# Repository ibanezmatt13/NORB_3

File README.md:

WARNING - There is a slight design issue with the schematic for the PCB which I had to bodge to get the micro SD working. The VSS pins of the connector should be connected to a GND point on the board, which for some reason it isn't. So, I had to solder a wire going from the connector to a ground point on the board; not pretty but it works.

There are two scripts here, one for delay-driven RTTY, and one for interrupt-driven RTTY. The delay-driven code has been flown and proved to work perfectly; the interrupt-driven code works fine on the ground but has not had an approval flight just yet.

NORB 3
======
NORB 3 is the third generation in the NORB AVR-based HAB tracking PCB series. 

Main Components:
================

NTX2 434MHz Radio Transmitter

Ublox MAX 7 GPS Module

Amtel ATMEGA328P-AU Microcontroller

SHT11 Temperature/Humidity Sensor

TMP102 I2C Temperature Sensor

Micro SD socket

TPS61201 Step-up Boost Regulator

Taoglas GPS Antenna

Info
====

More information including the development, current status and pictures of the tracker can be found at NORB's website:

                                                  http://www.norb.co.uk

What NORB does...
=================

The current software that runs the NORB board does several things:

1.  It uses a special routine to search repeatedly for certain characters over a serial connection to the Ublox GPS         module. Once it picks up the correct beginning of what could be a valid NMEA sentence, it checks for the letter G to     to see if it is the correct sentence. If it is, it passes the sentence as a string to a parse_NMEA function.

2.  The parse_NMEA function is designed to carefully assess whether the sentence contains any anomalies in certain          fields. This could be a lost character during transfer or the sentence may not actually reflect a full GPS lock.        Should this be the case, the parsing is discontinued and the search for another sentence restarts. If it does get       through however, a few tasks are performed...

3.  The time is checked to assess what format it is in and to assess if it is a valid time value. Then the                  Latitude/longitude is converted into decimal degrees for uploading to the spacenear.us server after decoding. 

4.  After the sentence has been stripped down and individual fields of data have been analysed, the program will request     information from the SHT11 temperature and humidity sensor where upon it will parse the data into a suitable format.     The voltage across the battery is also analysed by scaling the analogue value on the correct analogue pin to a value     within the range 0v to 3.3v.

5.  Next, two strings are constructed: a log_datastring and a send_datastring. The log_datastring contains absolutely       all data including voltage and humidity, which will be logged to the SD card. The send_datastring contains only the     bare minimum of required data for basic telemetry, but I couldn't resist adding temperature in there too. I have        done this to further reduce the probability of a decoding error on the ground. ie, more data coming down = more         chance of a bad sentence.

6.  Then, we log the log_datastring to the SD card, and send the send_datastring down over the radio link by splitting      it up into binary digits to toggle the transmit pin on our transmitter. And there you have it! :D

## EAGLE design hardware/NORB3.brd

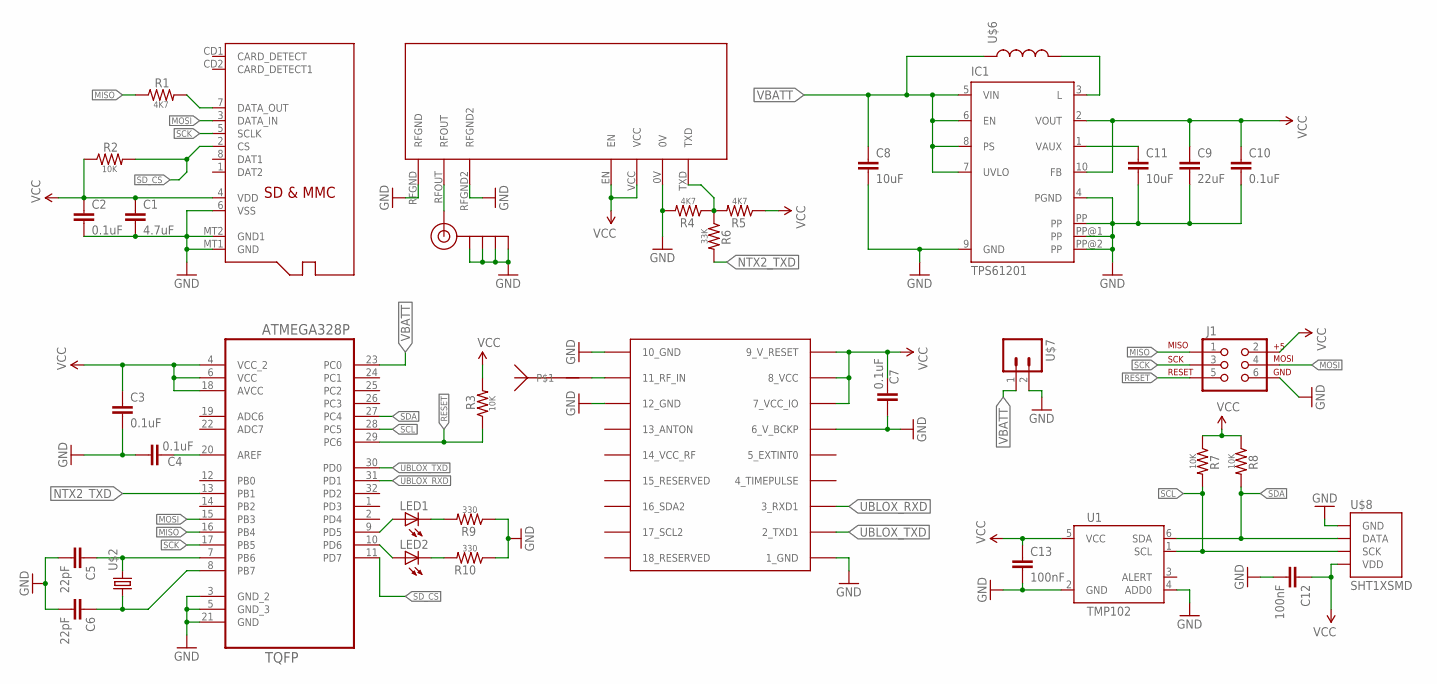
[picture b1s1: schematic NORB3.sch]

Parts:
C1: 4.7uF; 0603-CAP
C2, C3, C4, C7, C10: 0.1uF; 0603-CAP
C5, C6: 22pF; 0603-CAP
C8: 10uF; 1206
C9: 22uF; 1206
C11: 10uF; 0603-CAP
C12, C13: 100nF; 0603-CAP
IC1: TPS61201; S-PDSO-N10
J1: AVR_SPI_PRG_6PTH; 2X3
J$1: SMA_EDGE; SMA-EDGE
LED1, LED2: LEDCHIPLED_0805; CHIPLED_0805
R1, R4, R5: 4K7; 0603-RES
R2, R3, R7, R8: 10K; 0603-RES
R6: 33K; 0603-RES
R9, R10: 330; 0603-RES
U1: TMP102; SOT563
U2: ATMEGA328P-AU; QFP80P900X900X120-32N
U$1: MICROSD
U$2: ABRACON_ABM3_CRYSTALABM03_HC49; ABM03_HC49
U$3: UBLOX_MAX-6
U$4: TAOGLAS.GP.1575.18.2.A.02
U$5: NTX2
U$6: 2.2uH; ELLVGG_INDUCTOR
U$7: M02-NOSILK
U$8: SHT1XSMD; SHT1X

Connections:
GND: C3.2, C4.2, C5.2, C6.2, C7.2, C8.2, C9.2, C10.2, C11.2, C12.2, C13.2, IC1.4 (PGND), IC1.9 (GND), IC1.PP, IC1.PP@1 (PP), IC1.PP@2 (PP), J1.6, J$1.GND@0 (GND), J$1.GND@1 (GND), J$1.GND@2 (GND), J$1.GND@3 (GND), R4.2, R9.1, R10.1, U1.2 (GND), U1.4 (ADD0), U2.3 (GND_2), U2.5 (GND_3), U2.21 (GND), U$3.1_GND, U$3.6_V_BCKP, U$3.10_GND, U$3.12_GND, U$5.0V, U$5.RFGND, U$5.RFGND2, U$7.2, U$8.1 (GND)
MISO: J1.1, R1.1, U2.16 (PB4)
MOSI: J1.4, U2.15 (PB3), U$1.3 (DATA_IN)
unnamed: R1.2, U$1.7 (DATA_OUT)
unnamed: C5.1, U2.7 (PB6), U$2.2
unnamed: C4.1, U2.20 (AREF)
unnamed: C6.1, U2.8 (PB7), U$2.1
unnamed: U$3.11_RF_IN, U$4.P$1
unnamed: J$1.SIG (SIGNAL), U$5.RFOUT
unnamed: IC1.3 (L), U$6.P$2 (2)
unnamed: R4.1, R5.2, R6.1, U$5.TXD
unnamed: LED1.A, U2.9 (PD5)
unnamed: C11.1, IC1.1 (VAUX)
unnamed: LED1.C, R9.2
unnamed: LED2.A, U2.10 (PD6)
unnamed: LED2.C, R10.2
NTX2_TXD: R6.2, U2.13 (PB1)
RESET: J1.5, R3.1, U2.29 (PC6)
SCK: J1.3, U2.17 (PB5), U$1.5 (SCLK)
SCL: R7.2, U1.1 (SCL), U2.28 (PC5), U$8.3 (SCK)
SDA: R8.2, U1.6 (SDA), U2.27 (PC4), U$8.2 (DATA)
SD_CS: R2.2, U2.11 (PD7), U$1.2 (CS)
UBLOX_RXD: U2.31 (PD1), U$3.3_RXD1
UBLOX_TXD: U2.30 (PD0), U$3.2_TXD1
VBATT: C8.1, IC1.5 (VIN), IC1.6 (EN), IC1.7 (UVLO), IC1.8 (PS), U2.23 (PC0), U$6.P$1 (1), U$7.1
VCC: C1.1, C2.1, C3.1, C7.1, C9.1, C10.1, C12.1, C13.1, IC1.2 (VOUT), IC1.10 (FB), J1.2, R2.1, R3.2, R5.1, R7.1, R8.1, U1.5 (VCC), U2.4 (VCC_2), U2.6 (VCC), U2.18 (AVCC), U$1.4 (VDD), U$3.7_VCC_IO, U$3.8_VCC, U$3.9_V_RESET, U$5.EN, U$5.VCC, U$8.4 (VDD)
VSS: C1.2, C2.2, U$1.6 (VSS), U$1.MT1 (GND), U$1.MT2 (GND1)

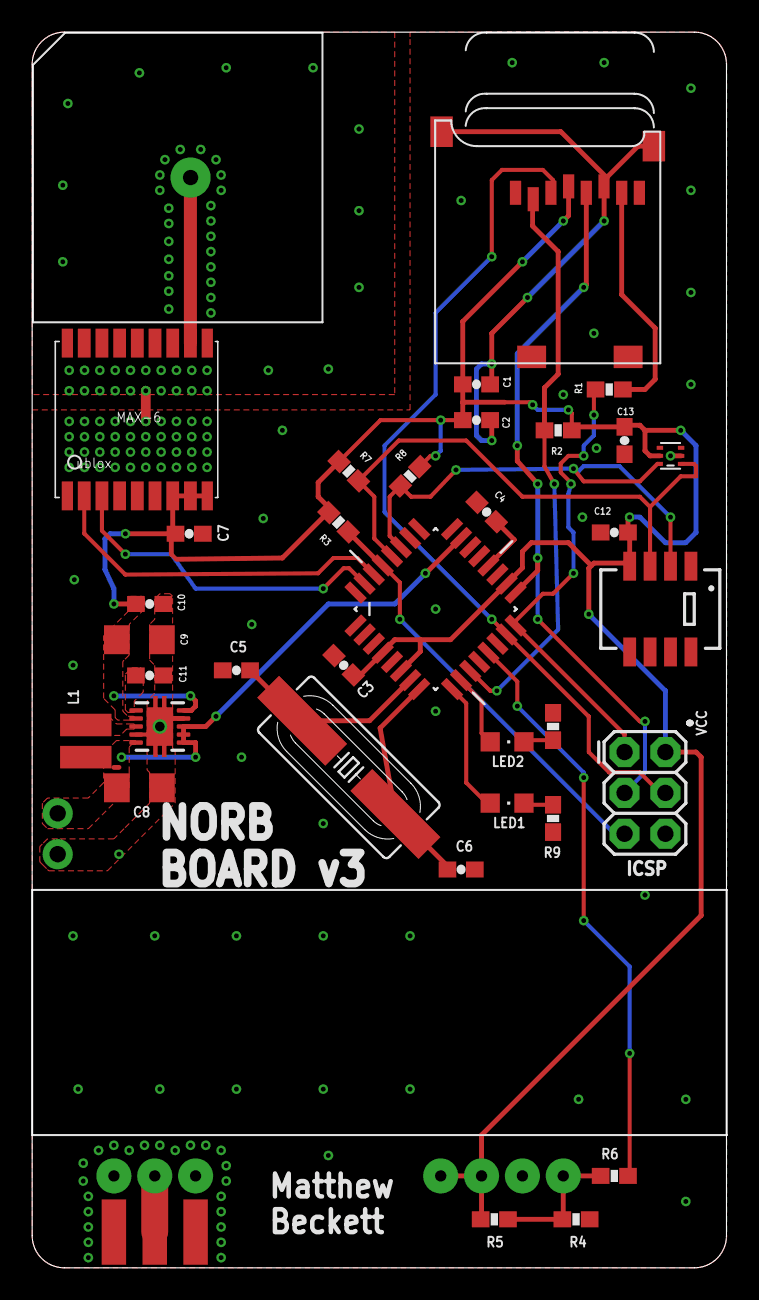
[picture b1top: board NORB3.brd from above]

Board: 2 copper layers, 43.2 x 76.8 mm, 38 parts (0 on the bottom side), 27 nets.

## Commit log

2013-10-14 Create testscript.cpp
    Not for use on tracker, purely for testing.
2013-10-25 Rename NORB3.cpp to NORB3.ino
2013-10-29 Create gh-pages branch via GitHub
2013-10-29 Rename NORB3.ino to software/NORB3.ino
2013-12-24 Create NORB.bas
    BASIC script to take a 2 minute video, save, take another 2 minute video, save, etc, in a loop for the whole flight!
    Will be eventually modified to accommodate intermittent picture taking.
2014-01-09 Update NORB.bas
    Basic script to take a 2 minute video and save in a loop throughout the flight. This avoids the max recording limit set on modern cameras for tax reasons.
2014-04-03 Create KMLCreator.py
    A quick python sketch to extract the latitude and longitude from a datafile and write to a new file for use in GEarth.
2014-04-07 Added interrupt code
    Note, SD not supported in this version

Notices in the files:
parts and their libraries:
SparkFun-Resistors: Licensing: CC v3.0 Share-Alike You are welcome to use this library for commercial purposes.
